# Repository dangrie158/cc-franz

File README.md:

#Camera Control 
##--> iPad controlled camera slider <--

<br /><br />
###Who we are
Hi, let’s introduce ourselves first: we are [Daniel Grießhaber](https://twitter.com/DanielGriehaber) and [Tobias Schneider](https://twitter.com/hpppxl), two master students (Computer Science and Media) of the Stuttgart Media University.

###TL;DR
Awesome, selfmade Camera Slider for ~180€ that can be controlled and programmed via an iPad app. If you read along you will find information on how to build one yourself!

###What this is
During the summer term of 2015 we developed a Camera Slider for controllable and repeatable time lapse and realtime shots. Since there are [already a couple DIY sliders](http://hackaday.com/2014/01/27/yet-another-diy-camera-slider/) out there, we wanted to give ours some special features to make it stick out from the masses:

###Awesome feature list:
#####2 motorized axis (linear movement and panning)
Most DIY Camera Sliders out there have only one remote axis. We have two (more is always better). ;-)
#####WiFi Access
Thanks to some recent development in WiFi integration we were able to add an iPad to control the Camera Slider.
#####iPad Control
There are two ways of controlling the Camera Slider. First of all, you can handle the slider via the live control and steer both axis independently. Furthermore, you can record your movement and save it for later playback.
 
Secondly, you can create simple scripts over an intuitive, graphical UI to program the slider for long duration shots (e.g. time lapse) with a slow, smooth and continuous movement that is repeatable until you are happy with the outcome.

## TOC

* [Mechanical Engineering](Slider/CAD/)
* [Electrical Engineering](Slider/Mainboard/)
* [ESP8266 WiFi Module](Slider/WiFi-Module/)
* [Microcontroller](Slider/Firmware/)

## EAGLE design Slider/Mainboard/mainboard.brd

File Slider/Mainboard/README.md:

###Electrical Engineering

#####BOM (What you need)

| Qty | Device                 | Package | Value  | Parts                                       | Description      |
|-----|------------------------|---------|--------|---------------------------------------------|------------------|
| 2   | A4988                  | DIP     | –      | U3, U4                                      |                  |
| 1   | ¼W Resistor            | 0207    | 100 kΩ | R15                                         |                  |
| 1   | Potentiometer          | CA9V    | 100 kΩ | R16                                         |                  |
| 8   | Ceramic Capacitor      | C050    | 100 nF | C1, C2, C4, C5, C6, E13, E14, E15           |                  |
| 2   | Electrolytic Capacitor | CA9V    | 100 µF | C4, C8                                      |                  |
| 5   | ¼W Resistor            | 0207    | 100 Ω  | R3, R4, R10, R11, R12                       |                  |
| 8   | ¼W Resistor            | 0207    | 10 kΩ  | R1, R2, R5, R6, R7, R8, R9, R14             |                  |
| 2   | Electrolytic Capacitor | CA9V    | 10 µF  | C3, C16                                     |                  |
| 1   | Power Check            | –       | –      | JP1                                         |                  |
| 1   | Crystal Oscillator     | HC49    | 16 MHz | Q1                                          |                  |
| 1   | Diode                  | DO41    | –      | D2                                          |                  |
| 4   | Electrolytic Capacitor | CA9V    | 1 µF   | C9, C10, C11, C12                           |                  |
| 2   | Ceramic Capacitor      | C050    | 22 pF  | C17, C18                                    |                  |
| 1   | LM33CV                 | TO22    | –      | IC2                                         |                  |
| 1   | 8705                   | TO22    | –      | IC1                                         |                  |
| 1   | Atmega328P             | DIL28   | –      | U1                                          |                  |
| 2   | BC337                  | TO92    | –      | T1, T2                                      | NPM Transistor   |
| 1   | 2 Pole Connector       | –       | –      | IROUT                                       |                  |
| 1   | 3 Pole Connector       | –       | –      | ENDSTOP                                     |                  |
| 3   | 4 Pole Connector       | –       | –      | MOT1, MOT2, RS232                           |                  |
| 1   | 2x3 Pin Header         | –       | –      | ICSP                                        |                  |
| 2   | 3 Channel DIP switch   | –       | –      | MSMOT1, MSMOT2                              |                  |
| 1   | ESP8266                | –       | –      | U5                                          |                  |
| 1   | LM358                  | DIL08   | –      | IC3                                         | jelly bean Opamp |
| 1   | MAX232                 | DIL16   | –      | U2                                          |                  |
| 1   | 5mm LED                | –       | –      | D1                                          |                  |
| 6   | Tactile Button         | –       | –      | HOMING, LEFT, RIGHT, TILTCCW, TILTCW, RESET |                  |

Total costs for electrical parts: <br />
**~ 39,33€ + shipping fees**

#####Schematic

We designed the schematic modular to get a good overview of the whole system and work independently on single modules. 

######Microcontroller (not labeled, the part in the center)
For the brain of our slider we’ve chosen an ATMEGA 328 from Atmel. The reason for this simply was the huge amount of information and tutorials out there for this chip. This is the same chip you have on the Arduino Uno, the one you may have in your parts bin.  Just for kicks (and maybe also because this was a requirement by our lecturer) we did not use the Arduino bootloader or libraries and programmed the chip directly through the ISP interface. <br />
The chip has an whopping 32kB of Flash and 2kB of RAM.

######Powersupply
For the operation of the Camera Slider we need 3 different voltage rails: +12V for the motors, +5V for the microcontroller and as a main logic level and +3.3V as the WiFi module supply voltage.<br />
The +12V line is directly connected to the main power jack, which is supplied by an external plug pack. The +12V are only fed through a diode to protect the circuit from reverse polarization, which results in a small voltage drop of about the typical 0.7V.
For the +5V a linear 7805 voltage regulator was used, which turns any input voltage from +7V - +35V into a regulated +5V. The aforementioned is accomplished by burning all the extra energy and turning it into heat. During normal operation our slider consumes about 300mA on the +5V rail and therefore the energy of

heat needs to be dissipated. For that reason we attached a small heatsink to the voltage regulator. <br />
The 3.3V rail is also regulated by a linear regulator, but this time with another output voltage. The input voltage comes from the +5V line, which means that the 7805 needs to supply the current for the +3.3V rail as well. However, directly attaching the regulator to the 12V would mean that it needs to dissipate all the power down to the 3.3V, wich would result in a drop voltage of 12V - 3.3V = 8.7V. This way, the heat is spread across the two regulators.

######ICSP & Reset Circuit
The ICSP connector is needed to program the ATMEGA microcontroller. It is a simple SPI bus with power supply and a connection to the RESET pin of the controller. To flash the controller, the programmer needs to set the RESET pin low and therefore keeps the microcontroller in its reset state during the flashing process. To start the microcontroller, one needs to keep the RESET pin high. For this reason the RESET pin is connected to the 5V rail with a 10kΩ pull-up resistor. <br />
For manually resetting the controller, we also added a switch to pull the pin low. 

######Motor Controller (x2)
To drive the motors, we used 2 A4988 motor drivers. They handle all the complex driving and enable us to microstep the motors, which results in an up to 16x higher resolution to drive the motor. <br />
The microstepping setting is not subject to change during operation. However, to be able to set the bits manually we simply added a 3 pole DIP switch to each driver which allows us to change the setting after laying out the board.<br />
One could also hard-wire the setting in the same board layout by not populating the switches, but solder in the connections directly.
The microcontroller can make the motor step (or microstep) by toggling the STEP pin of the controller for at least 1µs. The changing edge (HIGH to LOW or LOW to HIGH) doesn’t matter. The direction of the motor is controlled by setting the DIR pin HIGH or LOW.

######Endstop Amplifier
Designing the mechanical construction, we realized that it would be nice to detect a special position of the linear axis to have a known reference point we could align the axis reference system to. Of course, the simplest way to implement such a feature would be a simple switch with a small lever which gets pressed when the axis moves past a threshold at the end of the axis. However, the simplest solution always is the most boring solution, and since this is a project where we wanted to learn something, we have chosen a more sophisticated and nicer way instead.
The solution should be opto electrical by using a photocell to detect the threshold position. The output of the photocell is analog and we quickly realized that photocells are not very stable in variable lighting conditions, and since we wanted to be able to use the slider during day- and nighttime we needed a way to amplify the cells return value. <br />
To convert the analog signal into a digital, binary one, we could have used a schmitt trigger with a matching threshold voltage, but back then we did not know what this threshold voltage would be. For this reason we implemented the schmitt trigger using an opamp and a precision 10 turn resistor to set the threshold.

The LM358 is used in inverting amplification mode. While the voltage at the negative (inverting) input of the opamp is lower than the voltage at the positive (non-inverting)  input, the opamp drives its output high. <br />
R1 is the feedback resistor that mixes the output signal back into the non-inverting input. R2 and the variable resistor R5 form a voltage divider which sets the voltage of the non inverting input (ignoring the feedback for a moment). The voltage at the input of the opamp 

.

If we now assume that the variable resistor is set to e.g. 10kΩ, we can calculate an input voltage of

.

That’s our basic threshold. Now we assume that the voltage at the inverting input (this is the output of the photo cell) is lower than this threshold, let’s say 1V. The opamp now drives its output high. <br />
Now we basically have a voltage of 5V at the output of the opamp. We can simplify the circuit in this state into the following one:

As one can see, we simply connected R1 directly to 5V instead of the output. When you look closely , we have R5 and R1 now in parallel, we can see this more clearly if we move R1 next to R5:

Since R5 and R1 are now in parallel, we can simply replace them by a single resistor (assuming R5 would still be set at 10kΩ) with the value:

.

This changes the threshold because the ratio between the two resistors changed. The threshold is now at

.

As we can see, our threshold voltage was raised, which means our trigger actually triggers at 2.62V. <br />
Now, let’s assume the voltage at the inverting input to our amplifier is raised above those 2.62V. The opamp instantly drives the output low. We, once again, can present this state as an equivalent circuit diagram:

You can clearly see that R1 and R2 are now in parallel. We can calculate the resistance they have as

.

That’s of course the same value we calculated for the other state. The interesting thing, however, is that we now have another threshold voltage. We can calculate it as

.

This means we have a hysteresis area of

.

This means the amplifier outputs a high signal as soon as the input signal reaches at least 2.62V, but only goes low again, if the input drops lower than 2.38V. Without this hysteresis through the feedback resistor R1, the amplifier could oscillate if you apply exactly 2.5V to the input. <br />
Since R5 is a variable resistor, the threshold voltage of the amplifier can be set to almost anything between 0 and 5V, even after the board is assembled. You can do the math for any other value of R5 now.

######WiFi Module
The WiFi Module we used is the ESP8266 Chip on a breakout board. This chip has received a lot of attention already, because it is available for ~3€ each. This is ~86€ cheaper than the [official arduino wifi shield](http://www.amazon.de/Arduino-WiFi-Shield-Smart-Projects/dp/3645651985). With the shipped firmware, this chip is controllable over an AT command set over a serial RS232 connection. However we later changed the firmware with our custom one. To communicate with the main ATMEGA, however, we still used a RS232 connection.

######RS232 Debug Port
To debug the firmware we wanted a serial port just to write debug messages and states. Since the ATMEGA only has one hardware serial port we just connected the debug module of the schematic to two random pins and used the hardware serial port for the communication with the ESP8266. <br />
Today, everybody uses the RS232 protocol at TTL levels (0V-5V) with dupont wire. However, the original standard uses a [DB-9 connector](http://www.electronicsplanet.ch/Anschl/seriell.html) and logic levels of -/+15V. We wanted to stick with the original standard and for that reason, we needed to convert the TTL signal to the full +/-15V swing. The chip that accomplishes that is the [MAX232](http://www.ti.com/lit/ds/symlink/max232.pdf). The nice thing about it, is that it does not need a positive and negative 15V rail to generate the signals. It instead uses a charge-pump and is therefore lucky with a supply of 5V. If you can’t get bothered to use the old standard and do not plan to connect the controller to the com port of an old computer, you can simply not populate the capacitors C9-C12 and the MAX232 chip U2. The simply bridge the pins from the micro directly to the debug connector.

######IR Transmitter Driver
Most cameras have the ability to control the shutter over a simple infrared camera. Although most vendors sell the remote control as a separate product, the IR codes for most cameras are readily available in the internet. Just to be able to control the shutter, we added a jelly bean BC337 NPN transistor to drive the LED. The transistor to drive the LED is probably not necessary because the ATMEGA can source ~20mA and sink ~40mA from its I/O ports which should be more than enough for most modern LEDs. However, it would be to drive the LED directly and transistors are not that expensive. Again, if you don’t want the driver, you can simply not populate it.

######User Interface
For test reasons, and to be able to control the slider without having an iPad at hand, we implemented a user interface with five buttons. These buttons allow you to control the angular and linear axis of the slider. The fifth button did not have any meaning back then, but is now used to start a predefined script. Furthermore, every button can be used to toggle the LED for feedback purposes. <br />
We used external pulldown resistors although the ATMEGA has internal ones for all I/O pins. We’ve decided to use external ones because it is easy to lay traces underneath them. It would also be possible to replace the resistors R5-R9 with simple copper wire and use the internal pulldowns.

######Layout

The board should be milled on the CNC machine we also used for the aluminum parts. For this reason we tried to lay out the board single sided just because it is much easier for home production. We ended up using 18 jumper wires, which is a pretty good end result. If you don't have a CNC mashine and don't want to install eagle, we have a black and white version of the layout for etching [here](https://github.com/dangrie158/cc-franz/raw/develop/Docs/Pdf/mainboard_etch.pdf).

The general layout uses the same modular setup we designed into our schematic. Since we do not need any high speed data transmission lines, the board is rather simple and there were not many potential problems. However, some things we kept in mind include:

######Local regulation and power traces
You should avoid running your power traces across the whole board, just because the copper also has a resistance. This resistance is higher, the narrower and longer the trace is. For this reason, the high current +12V power traces for the motor supply are 50 mil wide and are kept as short as possible, thus the power jack is quite close to the motor controllers. <br />
Another problem is that a higher trace resistance means a higher current for the rail because the resistance needs to be overcome. For this reason, the regulation should always happen as close to the device as possible. This also reduces ripple on the trace from coupling with other digital I/O lines. Our 5V rail is needed all over the board, so there is not much we can do to optimize in this respect. The 3.3V rails, however, is only needed for the ESP8266 WiFi Module and thus the LM33CV regulator is placed right next to it.

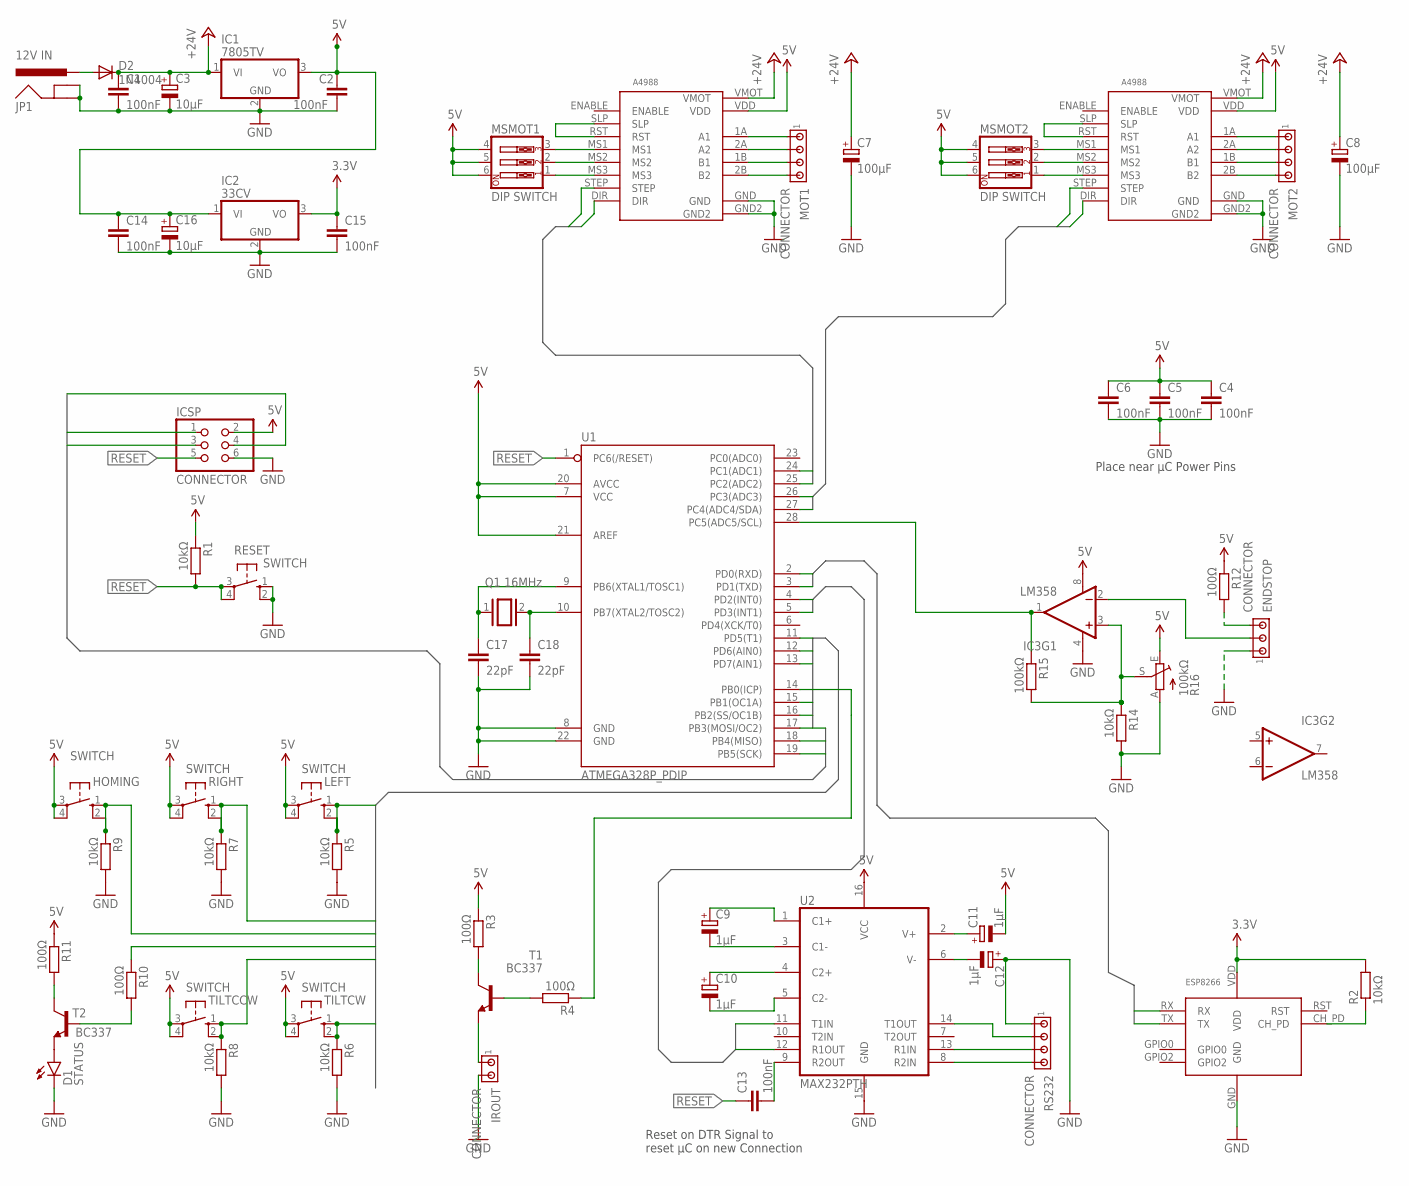
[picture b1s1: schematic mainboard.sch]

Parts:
C1, C2, C4, C5, C6, C13, C14, C15: 100nF; C050-024X044
C3, C16: 10µF; E2,5-6E
C7, C8: 100µF; E2,5-6E
C9, C10, C11, C12: 1µF; E2,5-6E
C17, C18: 22pF; C050-024X044
D1: STATUS; LED5MM
D2: 1N4004; DO41-10
ENDSTOP: CONNECTOR; 10X03MTA
HOMING: SWITCH; B3F-10XX
IC1: 7805TV; TO220V
IC2: 33CV; TO220V
IC3: LM358; DIP08
ICSP: CONNECTOR; 2X03
IROUT: CONNECTOR; 10X02MTA
JP1: 12V IN; POWER_JACK_SLOT
LEFT: SWITCH; B3F-10XX
MOT1, MOT2: CONNECTOR; 10X04MTA
MSMOT1, MSMOT2: DIP SWITCH; EDG-03
Q1: 16MHz; QS
R1, R2, R5, R6, R7, R8, R9, R14: 10kΩ; 0207/7
R3, R4, R10, R11, R12: 100Ω; 0207/7
R15: 100kΩ; 0207/7
R16: 100kΩ; CA9V
RESET: SWITCH; B3F-10XX
RIGHT: SWITCH; B3F-10XX
RS232: CONNECTOR; 10X04MTA
T1, T2: BC337; TO92
TILTCCW: SWITCH; B3F-10XX
TILTCW: SWITCH; B3F-10XX
U1: ATMEGA328P_PDIP; DIL28-3
U2: MAX232PTH; DIL16
U3, U4: A4988
U5: ESP8266

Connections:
3.3V: C15.1, IC2.3 (VO), R2.2, U5.VDD
5V: C2.1, C4.1, C5.1, C6.1, C11.-, C14.1, C16.+, HOMING.3, HOMING.4 (P1), IC1.3 (VO), IC2.1 (VI), IC3.8 (V+), ICSP.2, LEFT.3, LEFT.4 (P1), MSMOT1.4, MSMOT1.5, MSMOT1.6, MSMOT2.4, MSMOT2.5, MSMOT2.6, R1.1, R3.1, R11.1, R12.1, R16.E, RIGHT.3, RIGHT.4 (P1), TILTCCW.3, TILTCCW.4 (P1), TILTCW.3, TILTCW.4 (P1), U1.7 (VCC), U1.20 (AVCC), U1.21 (AREF), U2.16 (VCC), U3.VDD, U4.VDD
+24V: C1.1, C3.+, C7.+, C8.+, D2.C, IC1.1 (VI), U3.VMOT, U4.VMOT
DIR1: U1.24 (PC1(ADC1)), U3.DIR
DIR2: U1.26 (PC3(ADC3)), U4.DIR
ESPRX: U1.3 (PD1(TXD)), U5.RX
ESPTX: U1.2 (PD0(RXD)), U5.TX
GND: C1.2, C2.2, C3.-, C4.2, C5.2, C6.2, C7.-, C8.-, C12.+, C14.2, C15.2, C16.-, C17.2, C18.2, D1.K (C), ENDSTOP.1, IC1.2 (GND), IC2.2 (GND), IC3.4 (V-), ICSP.6, IROUT.2, JP1.GND@1 (GNDBREAK), JP1.GND@2 (GND), R5.2, R6.2, R7.2, R8.2, R9.2, R14.2, R16.A, RESET.1 (S), RESET.2 (S1), RS232.1, U1.8 (GND), U1.22 (GND), U2.15 (GND), U3.GND, U3.GND2, U4.GND, U4.GND2, U5.GND
HOMING: HOMING.1 (S), HOMING.2 (S1), ICSP.4, R9.1, U1.17 (PB3(MOSI/OC2))
LEFT: LEFT.1 (S), LEFT.2 (S1), R5.1, U1.11 (PD5(T1))
MISO: ICSP.1, U1.18 (PB4(MISO))
unnamed: U3.RST, U3.SLP
unnamed: MOT1.1, U3.1A (A1)
unnamed: MOT1.2, U3.2A (A2)
unnamed: MOT1.3, U3.1B (B1)
unnamed: MOT1.4, U3.2B (B2)
unnamed: MSMOT1.1, U3.MS3
unnamed: MSMOT1.2, U3.MS2
unnamed: MSMOT1.3, U3.MS1
unnamed: U4.RST, U4.SLP
unnamed: C13.2, U2.9 (R2OUT)
unnamed: MSMOT2.1, U4.MS3
unnamed: MSMOT2.2, U4.MS2
unnamed: MSMOT2.3, U4.MS1
unnamed: MOT2.1, U4.1A (A1)
unnamed: MOT2.2, U4.2A (A2)
unnamed: MOT2.3, U4.1B (B1)
unnamed: MOT2.4, U4.2B (B2)
unnamed: RS232.2, U2.14 (T1OUT)
unnamed: RS232.3, U2.13 (R1IN)
unnamed: C9.+, U2.1 (C1+)
unnamed: C9.-, U2.3 (C1-)
unnamed: C10.+, U2.4 (C2+)
unnamed: C10.-, U2.5 (C2-)
unnamed: C11.+, U2.2 (V+)
unnamed: C12.-, U2.6 (V-)
unnamed: RS232.4, U2.8 (R2IN)
unnamed: R2.1, U5.CH_PD
unnamed: R4.2, T1.2 (B)
unnamed: R3.2, T1.3 (C)
unnamed: IROUT.1, T1.1 (E)
unnamed: IC3.1 (OUT), R15.1, U1.28 (PC5(ADC5/SCL))
unnamed: D1.A, T2.1 (E)
unnamed: R10.2, T2.2 (B)
unnamed: R11.2, T2.3 (C)
unnamed: ENDSTOP.3, R12.2
unnamed: ENDSTOP.2, IC3.2 (-IN)
unnamed: IC3.3 (+IN), R14.1, R15.2, R16.S
unnamed: R4.1, U1.14 (PB0(ICP))
unnamed: C18.1, Q1.2, U1.10 (PB7(XTAL2/TOSC2))
unnamed: C17.1, Q1.1, U1.9 (PB6(XTAL1/TOSC1))
unnamed: D2.A, JP1.PWR
RESET: C13.1, ICSP.5, R1.2, RESET.3, RESET.4 (P1), U1.1 (PC6(/RESET))
RIGHT: R7.1, RIGHT.1 (S), RIGHT.2 (S1), U1.13 (PD7(AIN1))
RXD: U1.4 (PD2(INT0)), U2.12 (R1OUT)
SCK: ICSP.3, U1.19 (PB5(SCK))
STATUS: R10.1, U1.16 (PB2(SS/OC1B))
STEP1: U1.25 (PC2(ADC2)), U3.STEP
STEP2: U1.27 (PC4(ADC4/SDA)), U4.STEP
TILTCCW: R8.1, TILTCCW.1 (S), TILTCCW.2 (S1), U1.12 (PD6(AIN0))
TILTCW: R6.1, TILTCW.1 (S), TILTCW.2 (S1), U1.15 (PB1(OC1A))
TXD: U1.5 (PD3(INT1)), U2.11 (T1IN)

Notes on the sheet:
Reset on DTR Signal to reset µC on new Connection
Place near µC Power Pins

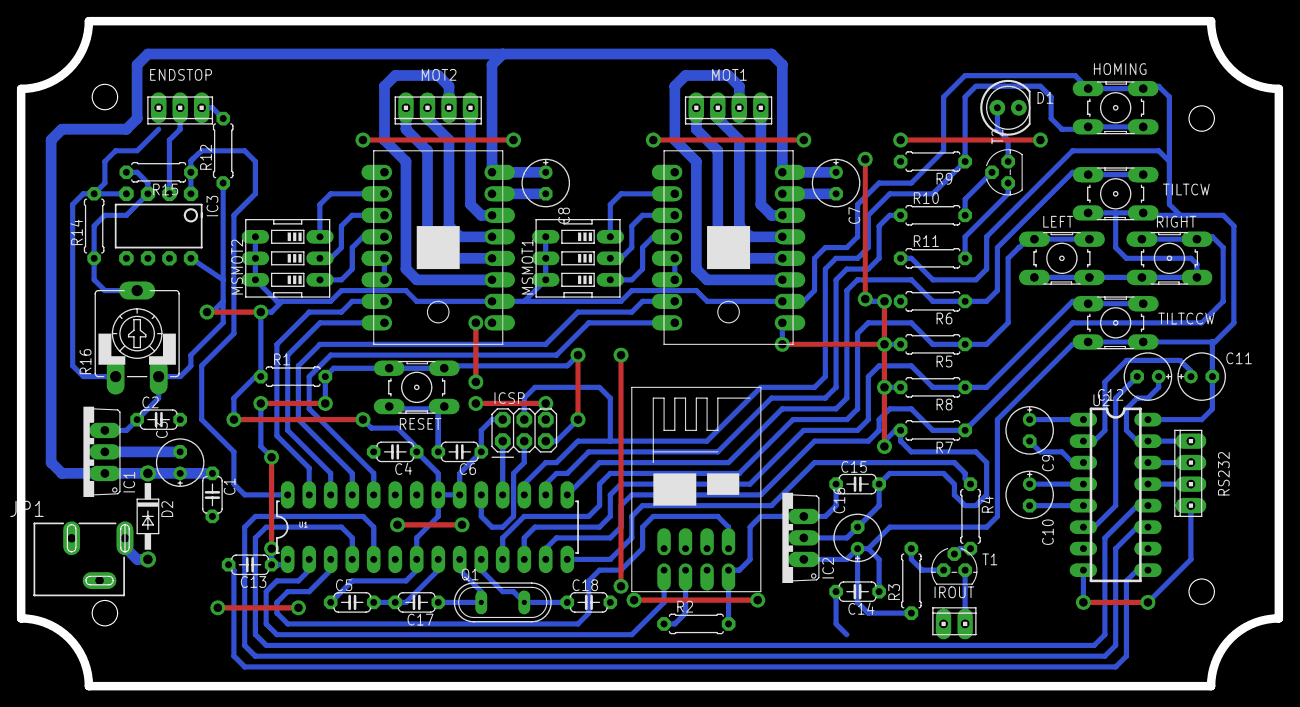
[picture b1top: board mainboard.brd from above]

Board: 2 copper layers, 148.5 x 78.5 mm, 61 parts (0 on the bottom side), 62 nets.

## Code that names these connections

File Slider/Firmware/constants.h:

#ifndef __CONSTANTS_H__
#define __CONSTANTS_H__

#include <avr/io.h>

/********************************/
/*        HELPER MACROS         */
/********************************/
#define SET(PORT,PIN) ((PORT) |= ((1) << (PIN)))
#define CLEAR(PORT,PIN) ((PORT) &= ~((1) << (PIN)))
#define TOGGLE(PORT,PIN) ((PORT) ^= ((1) << (PIN)))
#define ISSET(PORT, PIN) (((PORT) >> (PIN)) & (1))
#define VALUE(PORT, PIN, STATUS) (PORT) = (PORT) & ~((uintmax_t)(1) << (PIN)) | ((uintmax_t)(STATUS) << (PIN))

/********************************/
/*     VARIOUS DEFINITIONS      */
/*       FOR READABILITY        */
/********************************/
#define DIR_LEFT 1
#define DIR_RIGHT 0
#define DIR_CW 0
#define DIR_CCW 1

#define POSITION_DEBOUNCE_DELAY 100 //send positions every x microseconds

/********************************/
/*       SOFTWARE UART          */
/********************************/
#define SOFT_UART_BAUD_RATE 9600
#define SECONDS_TO_MICROSECONDS 1000000
#define SOFT_UART_BITTIME (SECONDS_TO_MICROSECONDS / SOFT_UART_BAUD_RATE) // 1/9600 BAUD = 104µS

/********************************/
/*       PIN DEFINITIONS        */
/********************************/

/************ OUTPUTS ***********/

#define MOTOR_DRIVER_PORT PORTC
#define MOTOR_DRIVER_DDR DDRC
#define LINEAR_DIR_PIN PC1
#define ANGULAR_DIR_PIN PC3
#define LINEAR_STEP_PIN PC2
#define ANGULAR_STEP_PIN PC4

#define LED_PORT PORTB
#define LED_DDR DDRB
#define LED_PIN PB2

#define IR_PORT PORTB
#define IR_DDR DDRB
#define IR_PIN PB0

#define SOFT_UART_PORT PORTD
#define SOFT_UART_DDR DDRD
#define SOFT_UART_TX_PIN PD3

/************* INPUTS ***********/

#define BUTTON_LEFT_PORT PIND
#define BUTTON_LEFT_DDR DDRD
#define BUTTON_LEFT_PIN PD5

#define BUTTON_RIGHT_PORT PIND
#define BUTTON_RIGHT_DDR DDRD
#define BUTTON_RIGHT_PIN PD7

#define BUTTON_CCW_PORT PIND
#define BUTTON_CCW_DDR DDRD
#define BUTTON_CCW_PIN PD6

#define BUTTON_CW_PORT PINB
#define BUTTON_CW_DDR DDRB
#define BUTTON_CW_PIN PB1

#define BUTTON_HOMING_PORT PINB
#define BUTTON_HOMING_DDR DDRB
#define BUTTON_HOMING_PIN PB3

#define ENDSTOP_TRIGGER_PORT PINC
#define ENDSTOP_TRIGGER_DDR DDRC
#define ENDSTOP_TRIGGER_PIN PC5

#endif //__CONSTANTS_H__

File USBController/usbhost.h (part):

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
/* SPI pin definitions. see avrpins.h   */
#if defined(__AVR_ATmega1280__) || (__AVR_ATmega2560__) || defined(__AVR_ATmega32U4__) || defined(__AVR_AT90USB646__) || defined(__AVR_AT90USB1286__)
typedef SPi< Pb1, Pb2, Pb3, Pb0 > spi;
#elif  defined(__AVR_ATmega168__) || defined(__AVR_ATmega328P__)
typedef SPi< Pb5, Pb3, Pb4, Pb2 > spi;
#elif defined(__AVR_ATmega644__) || defined(__AVR_ATmega644P__) || defined(__AVR_ATmega1284__) || defined(__AVR_ATmega1284P__)
typedef SPi< Pb7, Pb5, Pb6, Pb4 > spi;
#elif (defined(CORE_TEENSY) && (defined(__MK20DX128__) || defined(__MK20DX256__))) || defined(__ARDUINO_X86__) || defined(__MIPSEL__)
typedef SPi< P13, P11, P12, P10 > spi;
#elif defined(ARDUINO_SAM_DUE) && defined(__SAM3X8E__)
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
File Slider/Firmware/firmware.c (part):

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    SET(LED_DDR, LED_PIN); // set status LED as output
    SET(SOFT_UART_DDR, SOFT_UART_TX_PIN); // set TXD as output

    SET(MOTOR_DRIVER_DDR, ANGULAR_DIR_PIN); // set DIR1 as output
    SET(MOTOR_DRIVER_DDR, ANGULAR_STEP_PIN); // set STEP1 as output
    SET(MOTOR_DRIVER_DDR, LINEAR_DIR_PIN); // set DIR2 as output
    SET(MOTOR_DRIVER_DDR, LINEAR_STEP_PIN); // set STEP2 as output

    CLEAR(BUTTON_LEFT_DDR, BUTTON_LEFT_PIN); // set LEFT as input
    CLEAR(BUTTON_RIGHT_DDR, BUTTON_RIGHT_PIN); // set RIGHT as input
    CLEAR(BUTTON_CCW_DDR, BUTTON_CCW_PIN); // set CCW as input
    CLEAR(BUTTON_CW_DDR, BUTTON_CW_PIN); // set CW button as input
    CLEAR(BUTTON_HOMING_DDR, BUTTON_HOMING_PIN); // set HOMING as input
    CLEAR(ENDSTOP_TRIGGER_DDR, ENDSTOP_TRIGGER_PIN); // set ENDSTOP as input
}

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        SET(LED_PORT, LED_PIN); // switch on LED while button is pressed
        doAngularStep(DIR_CW);
    }
    else if (PINC >> PC5) { // endstop triggered

        SET(LED_PORT, LED_PIN); // LED on
    }
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
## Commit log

2015-04-04 added CAD drawings
    - added motor plate
    - added gear plate
    - added camera plate
    - added camera plate (bottom part)
    - added x axis sled
2015-04-04 addded autodesk backup files to gitignore
2015-04-24 added CAD drawing for Motorshaftcoupling
2015-04-24 changed logo setting to yellow/black
2015-04-25 Added firmware framework
2015-04-25 Added mainboard scheme with basic ABR setup
2015-04-27 changed logo background color
2015-04-28 added swift to gitignore
2015-04-28 added osx to gitignore
2015-04-28 added basic xcode project
2015-05-04 added SocketRocket dependency
2015-05-04 implement basic slider, reworked record button
2015-05-05 Added slider value change method
2015-05-05 added Web Socket Mock server
2015-05-06 added first layout (autolayout)
2015-05-13 added ConnectionManager
2015-05-15 refactorec connectionManager to CameraControl Object
2015-05-15 added A4988 to library
2015-05-15 Added Motor Drivers, Serial Interface and ICSP Header to schematic
2015-05-16 Completed schematic
    - added endstop amplifier
    - added user interface (switches for manual control)
    - added IR emitter circuit
    - created wifi module
    - added 3.3V rail
    - moved debug serial port to PD2 and PD3 (software emulated)
2015-05-16 small relayout of the schematic
    no functional changes
2015-05-16 added 16 MHZ Crystal with throughhole footprint
2015-05-16 small relayouting
2015-05-16 moved group designators to modules layer
2015-05-16 adjustments in layout and endstop amp
    - added adjustable resistor to voltage divider on positive opamp input in endstop amp to allow adjustment of triggerpoint
    - some layout fixes
2015-05-18 added board layout file with presorted module components
2015-05-18 Started layouting seperate modules
2015-05-19 Further board layouting
2015-05-22 progress in board layout and schematic
    - fixed the layout of the schematic after pin swapping
    - board connections all done
    - board layout all done
    - adjusted outline to match case
2015-05-22 switched from generic pinheaders to the right connector footprint
2015-06-01 added milling layer to board
2015-06-16 Added first version of the USB Controller files.
    Will be refactored in further release to be more
    independet from arduino based code but runs already
    independently from the arduino IDE in pure c/c++.
2015-06-20 added connection management for iOS app
2015-06-20 added some c garbage files to .gitignore
2015-06-20 added working debug serial port (9600 TX only)
2015-06-20 Added Recording Class that can play a recording
2015-06-20 added LCD Font view Library and first implementation of the timer view
2015-06-23 added code for pan movement buttons
2015-06-29 further app demo improvements
2015-06-29 Updated to XCode7 Beta and improved sending of data via wifi
2015-06-30 added uart functions and simple parsing of the mesage format
2015-06-30 removed sublime project files and added them to gitignore
2015-06-30 changed stepping method to delay less logic (async only)
2015-06-30 added new message parsing with hexadecimal speed values
2015-06-30 Pushed the USB Controller Part of CC-Franz projec to repository.
    A readme explains the content of the USB based software parts.
    USBController/README is this readme file.
    USBController/USB_Shield contains the AVR and USB Host Shield part
    USBController/WebSocket_Client contains the ESP8266 firmware part
2015-06-30 Updated README Message since we did not use PS3 Integration
2015-07-02 Changed sent string to hex
2015-07-21 added switchable slider movement control
2015-07-23 More detailed code comments, slight improvements.
    Some slight improvements, removed unnecessary stuff
    and added more detailed comments for better code understanding.
2015-07-25 added recording functionality without data store
2015-07-25 Add/Delete List items, persistant recordings
2015-07-26 Added and finalized playback view
2015-07-27 Styling styling styling
2015-07-27 added iOS Logo Master to LFS
2015-08-16 finished up live controller - cleaned up autolayout - added speed view - added homing butons - seperated controls and info view
2015-08-16 Started working on ScriptController
2015-08-17 Added Script class for scripting movements with working functionality
2015-08-18 Improved Styling of Script Control page
2015-08-22 Color Scriptcontrol Buttons
2015-08-22 added playback functionality and UI to script view
2015-08-23 fixed pinch scaling of the timeline view
2015-08-23 Added script modification functionality (save, load, addAction,...) + styling
2015-08-23 added popup class that disappears when tapped outside to avoid code duplication
2015-08-23 added drag and drop for the actions
2015-08-24 Styling for script controller, delte function for script actions
2015-08-25 added editing to script view
2015-08-25 hide and show playback indicator lines
2015-08-28 renamed drawings to english names
2015-08-31 added WiFi Module Firmware from Linux VM
2015-08-31 added some readme files
2015-08-31 Finished readme files
2015-08-31 Fixed type and missing image in microcontroller readme
2015-08-31 added microcontroller heading
2015-08-31 changed html table markup to markdown
2015-08-31 reformatted mechanical partslist as table
2015-09-01 Added image PDFs
2015-09-01 linked pdfs to schematic images
2015-09-01 fixed formatting of README
2015-09-01 refactored firmware and added functions for sending websocket messages over uart
2015-09-01 added message parsing to iOS app
2015-09-01 added link to black/white schematic for etching
2015-09-01 fixed constants.h bug
2015-09-03 added latest version of WiFi Firmware
2015-09-03 restored WiFi README from previous commit
2015-09-04 Fixed drag & drop bug
2015-09-04 Fixed firmware bugs and some styling changes in xcode
2015-09-07 Added App Screenshots

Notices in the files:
USBController/usbhost.h:
Copyright (C) 2011 Circuits At Home, LTD. All rights reserved.
General Public License version 2 (GPL2) as published by the Free Software
Foundation and appearing in the file GPL2.TXT included in the packaging of
this file. Please note that GPL2 Section 2[b] requires that all works based
parts and their libraries:
SparkFun-LED: Licensing: Creative Commons ShareAlike 4.0 International - https://creativecommons.org/licenses/by-sa/4.0
